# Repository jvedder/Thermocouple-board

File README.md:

# 4-channel Thermocouple PCB (MAX31855)
## Eagle CAD Schematic and PCB Layout
### Part Number: PCB100 Rev A

This design has 4 channels of **MAX31855** thermocouple amplifiers managed by
an **STM32F042K4** (or **'K6**) ARM Cortex-M0 processor.  Primary communication
and power is RS-485 over Cat 5 UTP Ethernet cables with a POE-like power scheme.
Both full and half-duplex communication schemes are supported. 

Secondary communication is over an **FTDI 232-TTL USB-to-UART** cable.  Direct
communication over **USB** to the STM32 is also supported by the layout (but
has not been tested). Each allow an instance of this board (perhaps without the
MAX31855 populated) to be the RS-485 controller and provide POE power to the
bus from either the USB connection or a 2x5.5 mm power connector.

The RJ-45 Pinout is compatible with the 8-pin modular connector pinout in
**ANSI E1.11-2008 (R2018)** 
 _DMX512-A Asynchronous Serial Digital Data Transmission Standard_  
but has not been tested for interoperability. 

Please note the RS-485 signal naming in this design matches the IC 
manufacturers' convention (A is non-inverting, B is inverting) which is
opposite the RS-485/RS-422 standard (A is inverting, B is non-inverting).

The RJ-45 pins selected for power are also compatible with 10/100 Base-T
Power over Ethernet (POE) in case of a cabling error. External power in the
range of 5V to 12V is supported, but there is little thermal margin on the
LDO at 12V. Lower than 5V is possible if the voltage drop over the cable
is managed.

### Part Number: PCB101 Rev A 

This revision:

- Adds a TPS25921 eFuse to the 2x5.5 mm connector that sources the POE power
injection to ensure that it is current limited.
- Inverts the polarity of the user button so that it can be used for the SMT32
boot loader function.
- Moves the FTDI USART port to PA9/PA10 to support the SMT32 boot loader
function.
- Moves the I2C port to pins PB6/PB7 (USART and I2C were swapped).
- Adds 3 pairs of holes for each channel so that the thermocouple leads can be
tied to the PCB for strain relief.
- Lengthens the PCB.
- Corrects pinout error on button orientation.

## License: ##

[MIT License](../master/LICENSE.txt)

----------------------

A portion of this design was leveraged from the 
**Adafruit Thermocouple Amplifier MAX31855 breakout board**. 
The Adafruit license is copied below. I support Adafruit's open-source hardware.

> Adafruit MAX31885 Thermocouple Amp breakout
> 
> These are the Eagle CAD files for the Adafruit MAX31885 Thermocouple Amp
> breakout:
> 
>   ----> http://www.adafruit.com/products/269
> 
> Adafruit invests time and resources providing this open source design,
> please support Adafruit and open-source hardware by purchasing products
> from Adafruit!
> 
> Thermocouples are very sensitive, requiring a good amplifier with a
> cold-compensation reference. The MAX31855K does everything for you, and can
> be easily interfaced with any microcontroller, even one without an analog
> input. This breakout board has the chip itself, a 3.3V regulator with 10uF
> bypass capacitors and level shifting circuitry, all assembled and tested.
> Comes with a 2 pin terminal block (for connecting to the thermocouple) and pin header (to plug into any breadboard or > perfboard). Goes great with our 1m K-type thermocouple. 
> 
> 
> All text above must be included in any redistribution
> 
> Designed by Limor Fried/Ladyada for Adafruit Industries.
> Creative Commons Attribution/Share-Alike, all text above must be included in
> any redistribution
>

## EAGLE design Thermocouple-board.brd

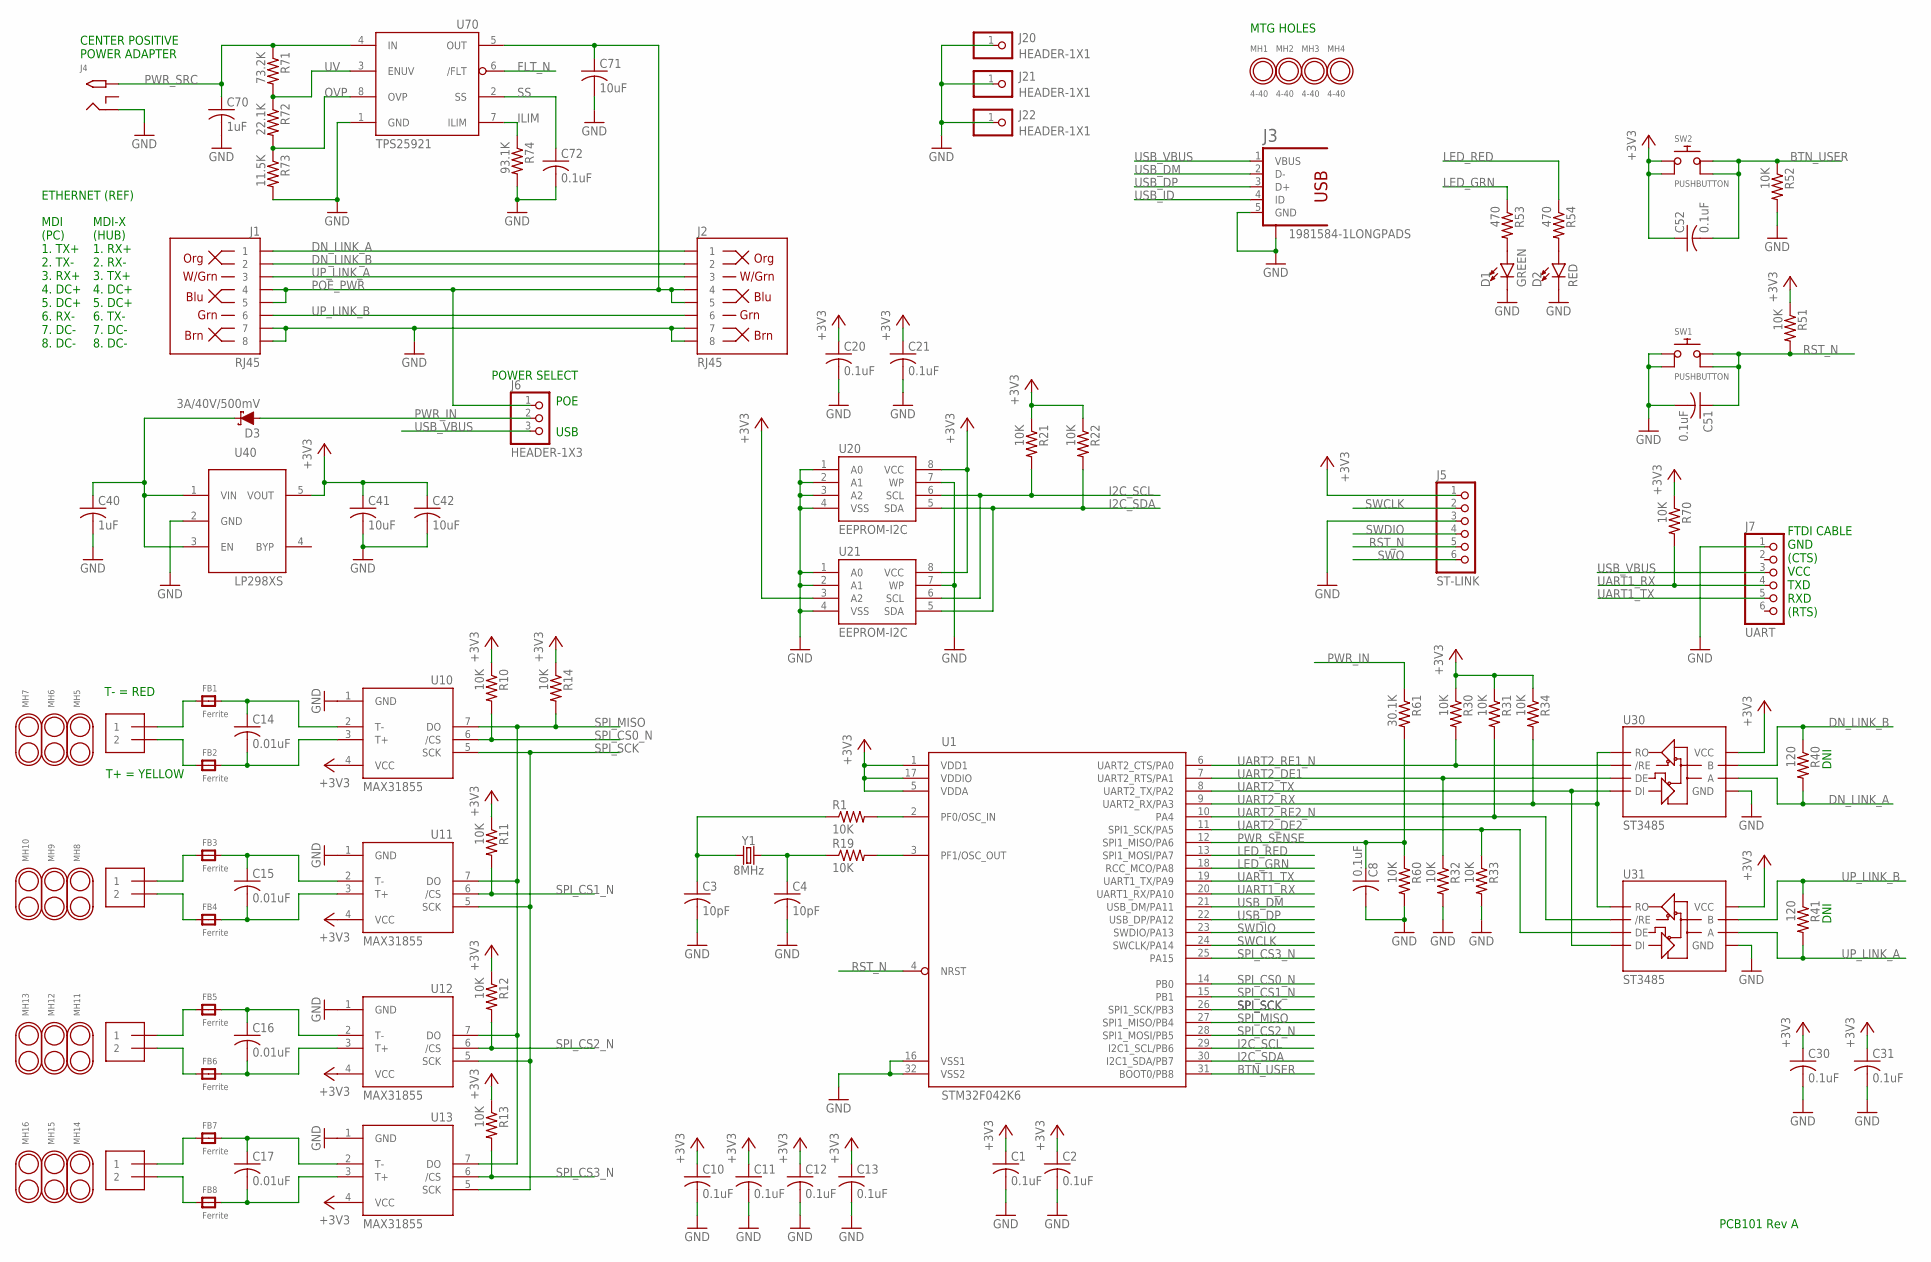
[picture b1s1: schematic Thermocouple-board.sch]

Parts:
C1, C2, C8, C10, C11, C12, C13, C20, C21, C30, C31, C51, C52, C72: 0.1uF; C0805K
C3, C4: 10pF; C0805K
C14, C15, C16, C17: 0.01uF; C0805K
C40, C70: 1uF; C0805K
C41, C42, C71: 10uF; C0805K
D1: GREEN; LED-0603
D2: RED; LED-0603
D3: 3A/40V/500mV; SMA-DIODE
FB1, FB2, FB3, FB4, FB5, FB6, FB7, FB8: Ferrite; _0805
J1, J2: RJ45; RJ45-8
J3: 1981584-1LONGPADS; 1981584-1-LONG
J4: 2.1MMJACKTHM; PJ-102A
J5: ST-LINK; 1X06_OVAL
J6: HEADER-1X3; 1X03_OVAL
J7: UART; 1X06_OVAL
J10, J11, J12, J13: 1X2-3.5MM
J20, J21, J22: HEADER-1X1; 1X01_OVAL
MH1, MH2, MH3, MH4: 4-40; MTG_HOLE_C280_H125
MH5, MH6, MH7, MH8, MH9, MH10, MH11, MH12, MH13, MH14, MH15, MH16: HOLD_DOWN
R1, R10, R11, R12, R13, R14, R19, R21, R22, R30, R31, R32, R33, R34, R51, R52, R60, R70: 10K; R0805
R40, R41: 120; R0805
R53, R54: 470; R0805
R61: 30.1K; R0805
R71: 73.2K; R0805
R72: 22.1K; R0805
R73: 11.5K; R0805
R74: 93.1K; R0805
SW1, SW2: PUSHBUTTON; PUSHBUTTON_6X6MM
U1: STM32F042K6; TQFP32-0.8MM
U10, U11, U12, U13: MAX31855; SO08
U20, U21: EEPROM-I2C; SO08
U30, U31: ST3485; SO08
U40: LP298XS; SOT23-5L
U70: TPS25921; SO08
Y1: 8MHz; HC49UP

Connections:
+3V3: C1.1, C2.1, C10.1, C11.1, C12.1, C13.1, C20.1, C21.1, C30.1, C31.1, C41.1, C42.1, C52.1, J5.1, R10.1, R11.1, R12.1, R13.1, R14.1, R21.1, R22.1, R30.1, R31.1, R34.1, R51.1, R70.1, SW2.1, SW2.2, U1.1 (VDD1), U1.5 (VDDA), U1.17 (VDDIO), U10.4 (VCC), U11.4 (VCC), U12.4 (VCC), U13.4 (VCC), U20.8 (VCC), U21.3 (A2), U21.8 (VCC), U30.8 (VCC), U31.8 (VCC), U40.5 (VOUT)
BTN_USER: C52.2, R52.1, SW2.3, SW2.4, U1.31 (BOOT0/PB8)
DN_LINK_A: J1.1, J2.1, R40.2, U30.6 (A)
DN_LINK_B: J1.2, J2.2, R40.1, U30.7 (B)
FLT_N: U70.6 (/FLT)
GND: C1.2, C2.2, C3.2, C4.2, C8.2, C10.2, C11.2, C12.2, C13.2, C20.2, C21.2, C30.2, C31.2, C40.2, C41.2, C42.2, C51.2, C70.2, C71.2, C72.2, D1.C, D2.C, J1.7, J1.8, J2.7, J2.8, J3.5 (GND), J3.S1, J4.RING, J5.3, J7.1, J20.1, J21.1, J22.1, R32.2, R33.2, R52.2, R60.2, R73.2, R74.2, SW1.1, SW1.2, U1.16 (VSS1), U1.32 (VSS2), U10.1 (GND), U11.1 (GND), U12.1 (GND), U13.1 (GND), U20.1 (A0), U20.2 (A1), U20.3 (A2), U20.4 (VSS), U20.7 (WP), U21.1 (A0), U21.2 (A1), U21.4 (VSS), U21.7 (WP), U30.5 (GND), U31.5 (GND), U40.2 (GND), U70.1 (GND)
I2C_SCL: R21.2, U1.29 (I2C1_SCL/PB6), U20.6 (SCL), U21.6 (SCL)
I2C_SDA: R22.2, U1.30 (I2C1_SDA/PB7), U20.5 (SDA), U21.5 (SDA)
ILIM: R74.1, U70.7 (ILIM)
LED_GRN: R53.1, U1.18 (RCC_MCO/PA8)
LED_RED: R54.1, U1.13 (SPI1_MOSI/PA7)
unnamed: FB1.1, J10.1
unnamed: R1.2, U1.2 (PF0/OSC_IN)
unnamed: R19.2, U1.3 (PF1/OSC_OUT)
unnamed: C14.1, FB1.2, U10.2 (T-)
unnamed: FB2.1, J10.2
unnamed: C14.2, FB2.2, U10.3 (T+)
unnamed: FB3.1, J11.1
unnamed: C15.1, FB3.2, U11.2 (T-)
unnamed: FB4.1, J11.2
unnamed: C15.2, FB4.2, U11.3 (T+)
unnamed: FB5.1, J12.1
unnamed: C16.1, FB5.2, U12.2 (T-)
unnamed: FB6.1, J12.2
unnamed: C16.2, FB6.2, U12.3 (T+)
unnamed: FB7.1, J13.1
unnamed: C17.1, FB7.2, U13.2 (T-)
unnamed: FB8.1, J13.2
unnamed: C17.2, FB8.2, U13.3 (T+)
unnamed: C4.1, R19.1, Y1.2
unnamed: C3.1, R1.1, Y1.1
unnamed: C40.1, D3.C, U40.1 (VIN), U40.3 (EN)
unnamed: D1.A, R53.2
unnamed: D2.A, R54.2
OVP: R72.2, R73.1, U70.8 (OVP)
POE_PWR: C71.1, J1.4, J1.5, J2.4, J2.5, J6.1, U70.5 (OUT)
PWR_IN: D3.A, J6.2, R61.1
PWR_SENSE: C8.1, R60.1, R61.2, U1.12 (SPI1_MISO/PA6)
PWR_SRC: C70.1, J4.TIP, R71.1, U70.4 (IN)
RST_N: C51.1, J5.5, R51.2, SW1.3, SW1.4, U1.4 (NRST)
SPI_CS0_N: R10.2, U1.14 (PB0), U10.6 (/CS)
SPI_CS1_N: R11.2, U1.15 (PB1), U11.6 (/CS)
SPI_CS2_N: R12.2, U1.28 (SPI1_MOSI/PB5), U12.6 (/CS)
SPI_CS3_N: R13.2, U1.25 (PA15), U13.6 (/CS)
SPI_MISO: R14.2, U1.27 (SPI1_MISO/PB4), U10.7 (DO), U11.7 (DO), U12.7 (DO), U13.7 (DO)
SPI_SCK: U1.26 (SPI1_SCK/PB3), U10.5 (SCK), U11.5 (SCK), U12.5 (SCK), U13.5 (SCK)
SS: C72.1, U70.2 (SS)
SWCLK: J5.2, U1.24 (SWCLK/PA14)
SWDIO: J5.4, U1.23 (SWDIO/PA13)
SWO: J5.6
UART1_RX: J7.4, R70.2, U1.20 (UART1_RX/PA10)
UART1_TX: J7.5, U1.19 (UART1_TX/PA9)
UART2_DE1: R32.1, U1.7 (UART2_RTS/PA1), U30.3 (DE)
UART2_DE2: R33.1, U1.11 (SPI1_SCK/PA5), U31.3 (DE)
UART2_RE1_N: R30.2, U1.6 (UART2_CTS/PA0), U30.2 (/RE)
UART2_RE2_N: R31.2, U1.10 (PA4), U31.2 (/RE)
UART2_RX: R34.2, U1.9 (UART2_RX/PA3), U30.1 (RO), U31.1 (RO)
UART2_TX: U1.8 (UART2_TX/PA2), U30.4 (DI), U31.4 (DI)
UP_LINK_A: J1.3, J2.3, R41.2, U31.6 (A)
UP_LINK_B: J1.6, J2.6, R41.1, U31.7 (B)
USB_DM: J3.2 (D-), U1.21 (USB_DM/PA11)
USB_DP: J3.3 (D+), U1.22 (USB_DP/PA12)
USB_ID: J3.4 (ID)
USB_VBUS: J3.1 (VBUS), J6.3, J7.3
UV: R71.2, R72.1, U70.3 (ENUV)

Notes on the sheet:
T+ = YELLOW
T- = RED
MDI-X (HUB) 1. RX+ 2. RX- 3. TX+ 4. DC+ 5. DC+ 6. TX- 7. DC- 8. DC-
MDI (PC) 1. TX+ 2. TX- 3. RX+ 4. DC+ 5. DC+ 6. RX- 7. DC- 8. DC-
ETHERNET (REF)
MTG HOLES
POWER SELECT
CENTER POSITIVE POWER ADAPTER
POE
USB
FTDI CABLE GND (CTS) VCC TXD RXD (RTS)
PCB101 Rev A
DNI

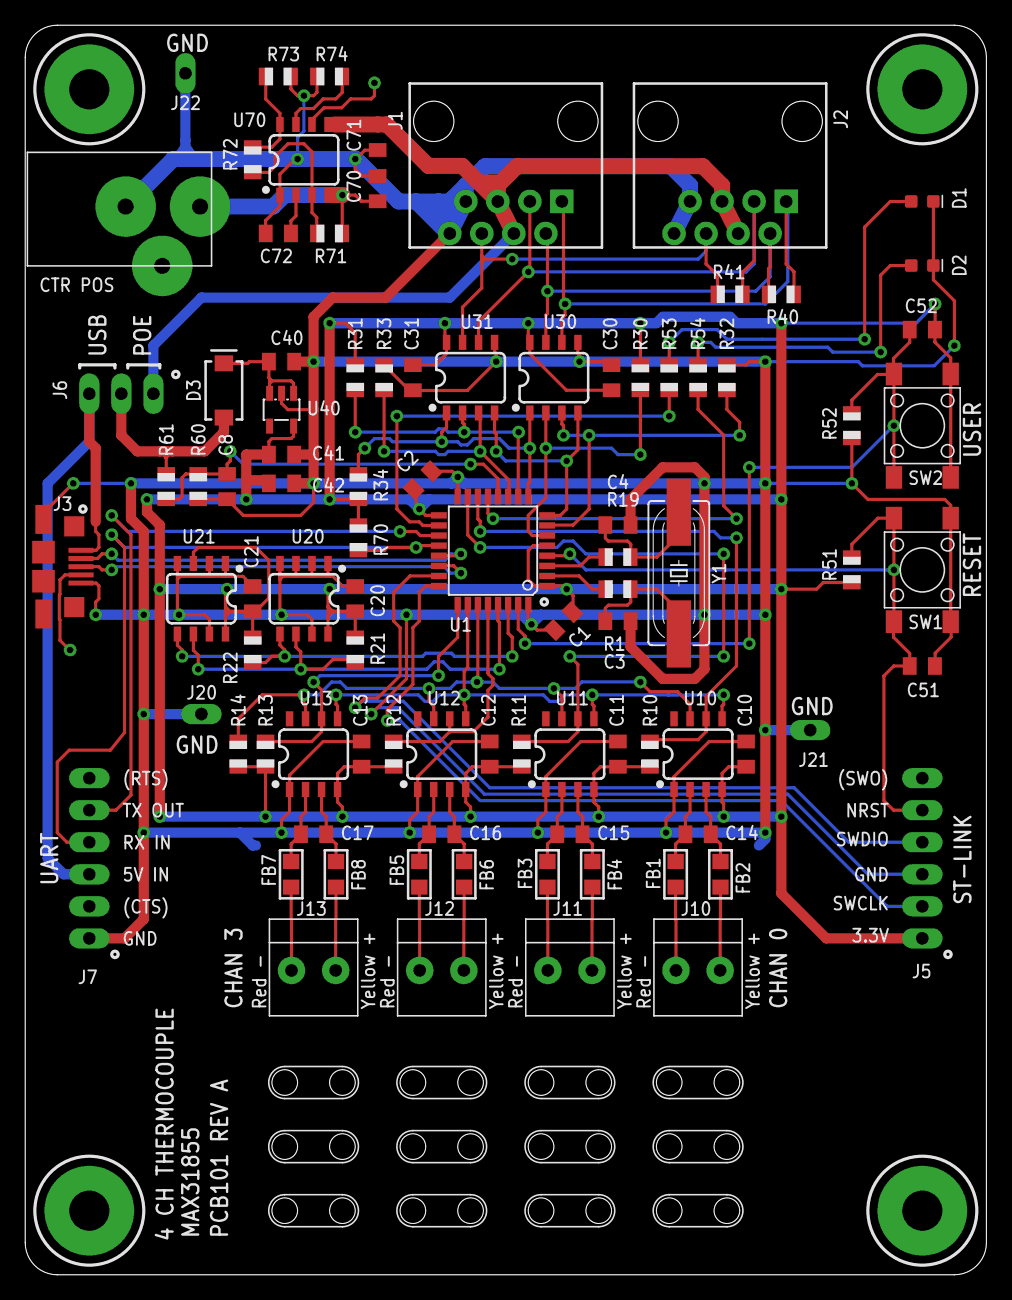
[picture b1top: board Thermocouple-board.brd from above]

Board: 2 copper layers, 76.2 x 99.1 mm, 107 parts (0 on the bottom side), 62 nets.

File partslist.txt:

Partlist

Exported from Thermocouple-board.brd at 12/27/18 10:27 PM

EAGLE Version 9.2.2 Copyright (c) 1988-2018 Autodesk, Inc.

Assembly variant: 

Part     Value          Package            Library                 Position (inch)       Orientation

C1       0.1uF          C0805K             adafruit                (1.78 1.24)           R225
C2       0.1uF          C0805K             adafruit                (1.34 1.68)           R45
C3       10pF           C0805K             adafruit                (1.95 1.24)           R0
C4       10pF           C0805K             adafruit                (1.95 1.54)           R0
C8       0.1uF          C0805K             adafruit                (0.72 1.66)           R270
C10      0.1uF          C0805K             adafruit                (2.32 0.82)           R90
C11      0.1uF          C0805K             adafruit                (1.93 0.82)           R90
C12      0.1uF          C0805K             adafruit                (1.54 0.82)           R90
C13      0.1uF          C0805K             adafruit                (1.15 0.82)           R90
C14      0.01uF         C0805K             adafruit                (2.17 0.57)           R0
C15      0.01uF         C0805K             adafruit                (1.78 0.57)           R0
C16      0.01uF         C0805K             adafruit                (1.39 0.57)           R0
C17      0.01uF         C0805K             adafruit                (1 0.57)              R0
C20      0.1uF          C0805K             adafruit                (0.59 1.28)           R270
C21      0.1uF          C0805K             adafruit                (0.91 1.28)           R270
C30      0.1uF          C0805K             adafruit                (1.93 2)              R90
C31      0.1uF          C0805K             adafruit                (1.31 2)              R270
C40      1uF            C0805K             adafruit                (0.9 2.05)            R0
C41      10uF           C0805K             adafruit                (0.9 1.76)            R0
C42      10uF           C0805K             adafruit                (0.9 1.67)            R0
C51      0.1uF          C0805K             adafruit                (2.6 1.51)            R180
C52      0.1uF          C0805K             adafruit                (2.59 1.94)           R180
D1       GREEN          LED-0603           SparkFun-LED            (2.24 2)              R90
D2       RED            LED-0603           SparkFun-LED            (2.33 2)              R90
D3       3A/40V/500mV   SMA-DIODE          SparkFun-DiscreteSemi   (0.72 1.96)           R90
FB1      Ferrite        _0805              microbuilder            (2.1 0.42)            R90
FB2      Ferrite        _0805              microbuilder            (2.24 0.42)           R90
FB3      Ferrite        _0805              microbuilder            (1.71 0.42)           R90
FB4      Ferrite        _0805              microbuilder            (1.85 0.42)           R90
FB5      Ferrite        _0805              microbuilder            (1.32 0.42)           R90
FB6      Ferrite        _0805              microbuilder            (1.46 0.42)           R90
FB7      Ferrite        _0805              microbuilder            (0.93 0.42)           R90
FB8      Ferrite        _0805              microbuilder            (1.07 0.42)           R90
J1       RJ45           RJ45-8             SparkFun-Connectors     (0.3 2.44)            R270
J2       RJ45           RJ45-8             SparkFun-Connectors     (2.7 2.44)            R90
J3       1981584-1      1981584-1          audio amplifier example (0 1.41)              R270
J4       2.1MMJACKTHM   PJ-102A            adafruit                (1.12 2.93)           R0
J5       ST-LINK        1X06_OVAL          Thermocouple-board      (2.8 0.75)            R90
J6       HEADER-1X3     1X03_OVAL          Thermocouple-board      (0.22 1.89)           R180
J7       UART           1X06_OVAL          Thermocouple-board      (0.2 0.75)            R270
J10      1X2-3.5MM      1X2-3.5MM          Thermocouple-board      (2.17 0.145)          R180
J11      1X2-3.5MM      1X2-3.5MM          Thermocouple-board      (1.78 0.145)          R180
J12      1X2-3.5MM      1X2-3.5MM          Thermocouple-board      (1.39 0.145)          R180
J13      1X2-3.5MM      1X2-3.5MM          Thermocouple-board      (1 0.145)             R180
MH1      4-40           MTG_HOLE_C280_H125 Thermocouple-board      (0.18 0.18)           R0
MH2      4-40           MTG_HOLE_C280_H125 Thermocouple-board      (2.82 0.18)           R0
MH3      4-40           MTG_HOLE_C280_H125 Thermocouple-board      (0.18 2.92)           R0
MH4      4-40           MTG_HOLE_C280_H125 Thermocouple-board      (2.82 2.92)           R0
R1       10K            R0805              adafruit                (1.95 1.34)           R180
R10      10K            R0805              adafruit                (2.02 0.82)           R90
R11      10K            R0805              adafruit                (1.63 0.82)           R90
R12      10K            R0805              adafruit                (1.24 0.82)           R90
R13      10K            R0805              adafruit                (0.85 0.82)           R90
R14      10K            R0805              adafruit                (0.76 0.82)           R90
R19      10K            R0805              adafruit                (1.95 1.44)           R180
R21      10K            R0805              adafruit                (0.59 1.45)           R90
R22      10K            R0805              adafruit                (0.91 1.45)           R90
R30      10K            R0805              adafruit                (2.02 2)              R270
R31      10K            R0805              adafruit                (1.13 2)              R270
R32      10K            R0805              adafruit                (2.11 2)              R90
R33      10K            R0805              adafruit                (1.22 2)              R90
R34      10K            R0805              adafruit                (1.14 1.66)           R90
R51      10K            R0805              adafruit                (2.6 1.39)            R0
R52      10K            R0805              adafruit                (2.59 1.82)           R0
R53      470            R0805              adafruit                (2.24 1.83)           R90
R54      470            R0805              adafruit                (2.33 1.83)           R90
R60      10K            R0805              adafruit                (0.63 1.66)           R270
R61      10K            R0805              adafruit                (0.54 1.66)           R270
R70      10K            R0805              adafruit                (0.63 0.93)           R90
SW1      PUSHBUTTON     PUSHBUTTON_6X6MM   Thermocouple-board      (2.81 1.45)           R270
SW2      PUSHBUTTON     PUSHBUTTON_6X6MM   Thermocouple-board      (2.81 1.88)           R270
U1       STM32F042K4    TQFP32-0.8MM       Thermocouple-board      (1.56 1.46)           R180
U10      MAX31855       SO08               adafruit                (2.17 0.82)           R0
U11      MAX31855       SO08               adafruit                (1.78 0.82)           R0
U12      MAX31855       SO08               adafruit                (1.39 0.82)           R0
U13      MAX31855       SO08               adafruit                (1 0.82)              R0
U20      EEPROM-I2C     SO08               Thermocouple-board      (0.75 1.28)           R0
U21      EEPROM-I2C     SO08               Thermocouple-board      (1.07 1.28)           R0
U30      ST3485         SO08               SparkFun-IC-Comms       (1.75 2)              R0
U31      ST3485         SO08               SparkFun-IC-Comms       (1.49 2)              R0
U40      LP298XS        SOT23-5L           adafruit                (0.9 1.9)             R180
Y1       8MHz           HC49UP             SparkFun-Clocks         (2.14 1.39)           R90

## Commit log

2018-11-30 Last with 74LVC1G125
2018-11-30 WIP Updating with RS-485 transceivers
2018-12-05 WIP Routing
2018-12-14 Start of move to STM32F042K4 with USB
2018-12-15 Ripup and start rerouting with USB and Xtal
2018-12-16 Before replacement of EEPROM
2018-12-16 Added README
2018-12-17 Wip routing. Updated DRC to Sparkfun and 20 mil vias with 10 mil annualar ring
2018-12-18 First pass routing commplete
2018-12-18 Upgraded diodes; start of adding 5.5/2.5mm power connector
2018-12-19 Lengthen board to 3.5in. Added power select jumpers
2018-12-21 Before placement rejigger
2018-12-22 start of placement rejigger
2018-12-22 Routing complete
2018-12-22 Cleanup errors
2018-12-22 More Cleanup
2018-12-25 WIP on larger MTG holes
2018-12-26 Reconfigured UARTs for FTDI cable
2018-12-26 Finish routing.
2018-12-27 Finish cleanup. Added schem frame.
2018-12-27 Added notes to UART connector
2018-12-28 Added Teardrops and released Gerbers
2018-12-30 Updated BOM and README.md
2019-01-04 rename output zip file
2019-01-11 revert .brd to pre-teardrops
2019-02-18 Added PDF folder
2019-02-18 Fix pushbutton and SO08. Start of efuse.
2019-02-19 RJ-45 rework routing WIP
2019-02-20 Routing WIP
2019-02-21 Extended PCB length to 3.9 in
2019-02-21 Updated micro USB conn to long pads
2019-02-23 Mostly routed. Needs connector alignment and hold downs.
2019-02-24 Added ground TPs
2019-02-24 Moved LEDs to uper right corner
2019-02-24 Reroute efuse
2019-02-25 PCB101_A Released and ordered
2019-02-25 Cleanup filenames; add PDFs
2019-02-25 Added PCB100_A
2019-02-25 Move PCB100_A to release folder
2019-02-25 Fix view on PCB101_A.brd
2019-03-21 Update values on schematic
2020-07-16 Add MIT License. Update README.
2020-07-16 Add file extension to LICENSE.txt

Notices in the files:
parts and their libraries:
SparkFun-Connectors: Licensing: Creative Commons ShareAlike 4.0 International - https://creativecommons.org/licenses/by-sa/4.0
